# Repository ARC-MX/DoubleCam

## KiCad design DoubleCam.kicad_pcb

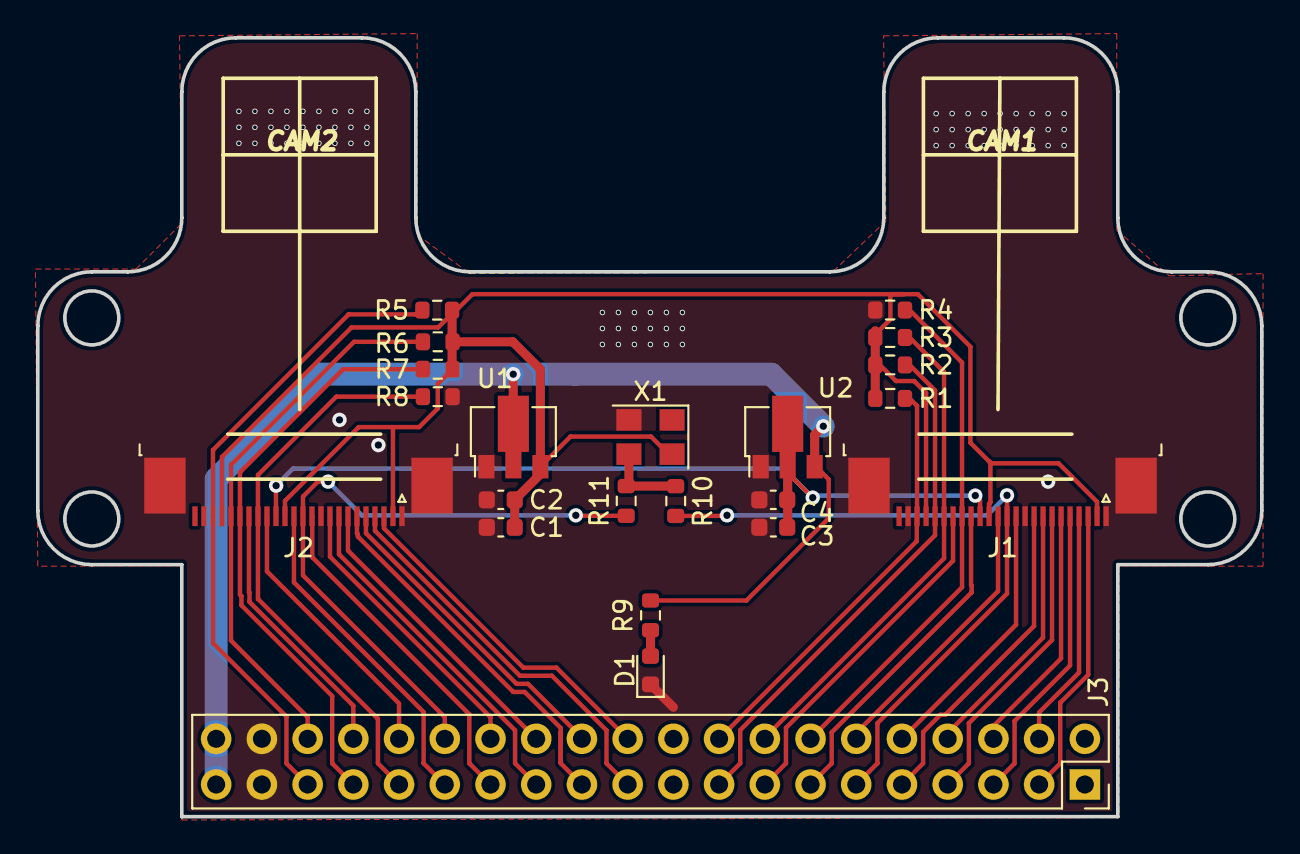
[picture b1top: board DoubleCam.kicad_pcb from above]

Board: 2 copper layers, 68.0 x 43.3 mm, 22 parts (0 on the bottom side), 38 nets.

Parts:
C1, C2, C3, C4: 104; C_0603_1608Metric
D1: TSAL4400; LED_0603_1608Metric
J1, J2: Conn_01x24_MountingPin; TE_2-1734839-4_1x24-1MP_P0.5mm_Horizontal
J3: Conn_02x20_Odd_Even; PinSocket_2x20_P2.54mm_Vertical
R1, R2, R3, R4, R5, R6, R7, R8, R9, R10, R11: R; R_0603_1608Metric
U1, U2: XC6206PxxxMR; SOT-89-3
X1: SG-3225CAN; Oscillator_SMD_SeikoEpson_SG8002CE-4Pin_3.2x2.5mm

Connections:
+1V5: C3.1, C4.1, J1.15, J2.15, U2.2
+2V8: C1.1, C2.1, J1.2, J1.14, J1.21, J2.2, J2.14, J2.21, R1.1, R2.1, R3.1, R5.1, R6.1, R7.1, U1.3, X1.4
+3V3: J3.39, J3.40, R9.1, U1.2, U2.3
/OV1_D0: J1.6, J3.6
/OV1_D1: J1.4, J3.4
/OV1_D2: J1.3, J3.3
/OV1_D3: J1.5, J3.5
/OV1_D4: J1.7, J3.7
/OV1_D5: J1.9, J3.9
/OV1_D6: J1.11, J3.10
/OV1_D7: J1.13, J3.12
/OV1_HREF: J1.16, J3.13
/OV1_PCLK: J1.8, J3.8
/OV1_PWDN: J1.17, J3.14, R4.1
/OV1_RESET: J1.19, J3.16, R3.2
/OV1_SCL: J1.20, J3.17, R2.2
/OV1_SDA: J1.22, J3.18, R1.2
/OV1_VSYNC: J1.18, J3.15
/OV1_XCLK: J1.12, J3.11, R10.1
/OV2_D0: J2.6, J3.23
/OV2_D1: J2.4, J3.21
/OV2_D2: J2.3, J3.22
/OV2_D3: J2.5, J3.24
/OV2_D4: J2.7, J3.26
/OV2_D5: J2.9, J3.28
/OV2_D6: J2.11, J3.27
/OV2_D7: J2.13, J3.29
/OV2_HREF: J2.16, J3.32
/OV2_PCLK: J2.8, J3.25
/OV2_PWDN: J2.17, J3.31, R8.1
/OV2_RESET: J2.19, J3.33, R7.2
/OV2_SCL: J2.20, J3.36, R6.2
/OV2_SDA: J2.22, J3.35, R5.2
/OV2_VSYNC: J2.18, J3.34
/OV2_XCLK: J2.12, J3.30, R11.1
GND: C1.2, C2.2, C3.2, C4.2, D1.1, J1.1, J1.10, J1.23, J1.MP, J2.1, J2.10, J2.23, J2.MP, J3.37, J3.38, R4.2, R8.2, U1.1, U2.1, X1.2
unnamed: D1.2, R9.2
unnamed: R10.2, R11.2, X1.3

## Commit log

2020-12-28 changed FPC connect
2020-12-28 Change FPC Connect
2021-03-12 修改等长线
